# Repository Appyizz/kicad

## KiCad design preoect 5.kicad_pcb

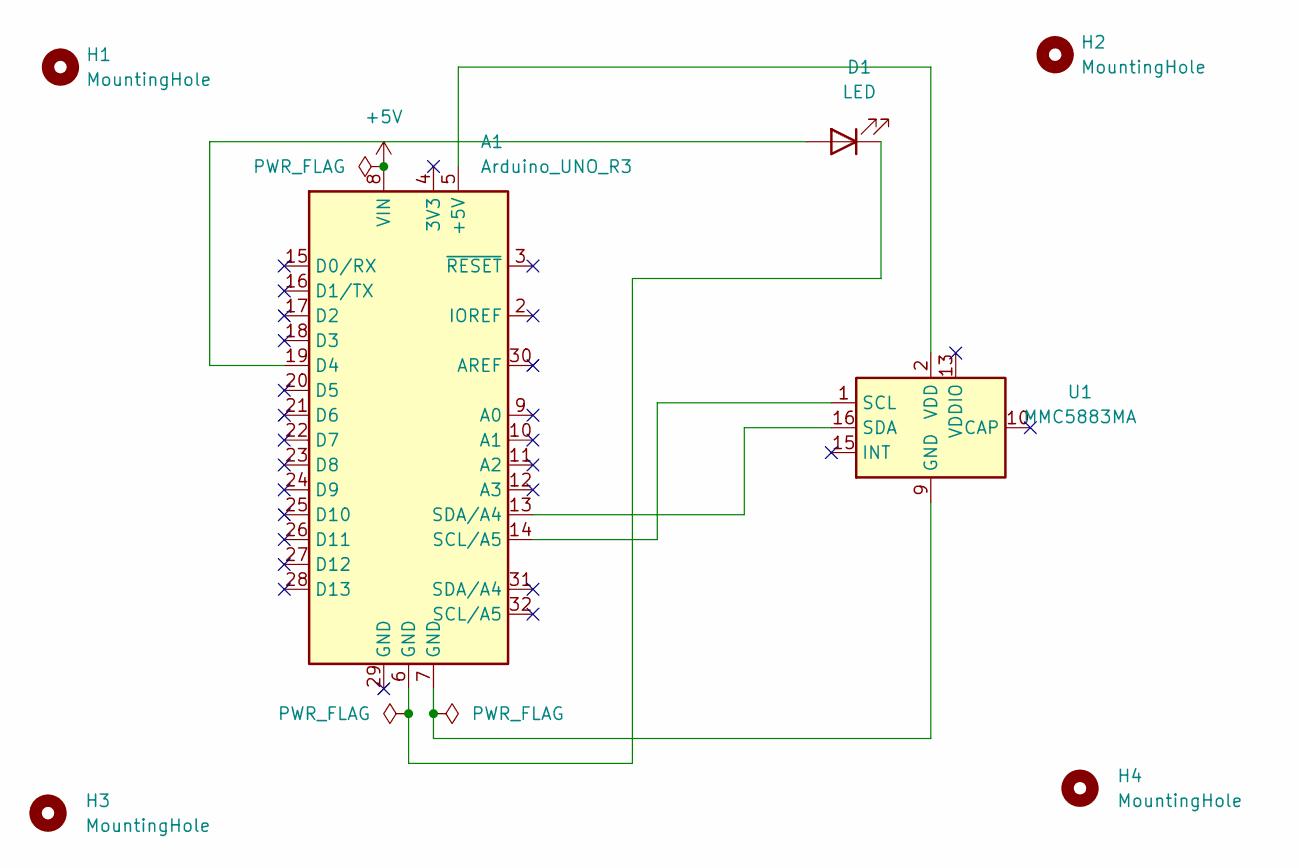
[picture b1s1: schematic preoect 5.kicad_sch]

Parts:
A1: Arduino_UNO_R3
D1: LED; LED_D4.0mm
H1, H2, H3, H4: MountingHole; MountingHole_2.5mm
U1: MMC5883MA; LGA-16_3x3mm_P0.5mm

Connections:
+5V: A1.8 (VIN)
unnamed: A1.5 (+5V), U1.2 (VDD)
unnamed: A1.19 (D4), D1.2 (A)
unnamed: A1.7 (GND), U1.9 (GND), U1.11 (GND)
unnamed: A1.6 (GND), D1.1 (K)
unnamed: A1.14 (SCL/A5), U1.1 (SCL)
unnamed: A1.13 (SDA/A4), U1.16 (SDA)

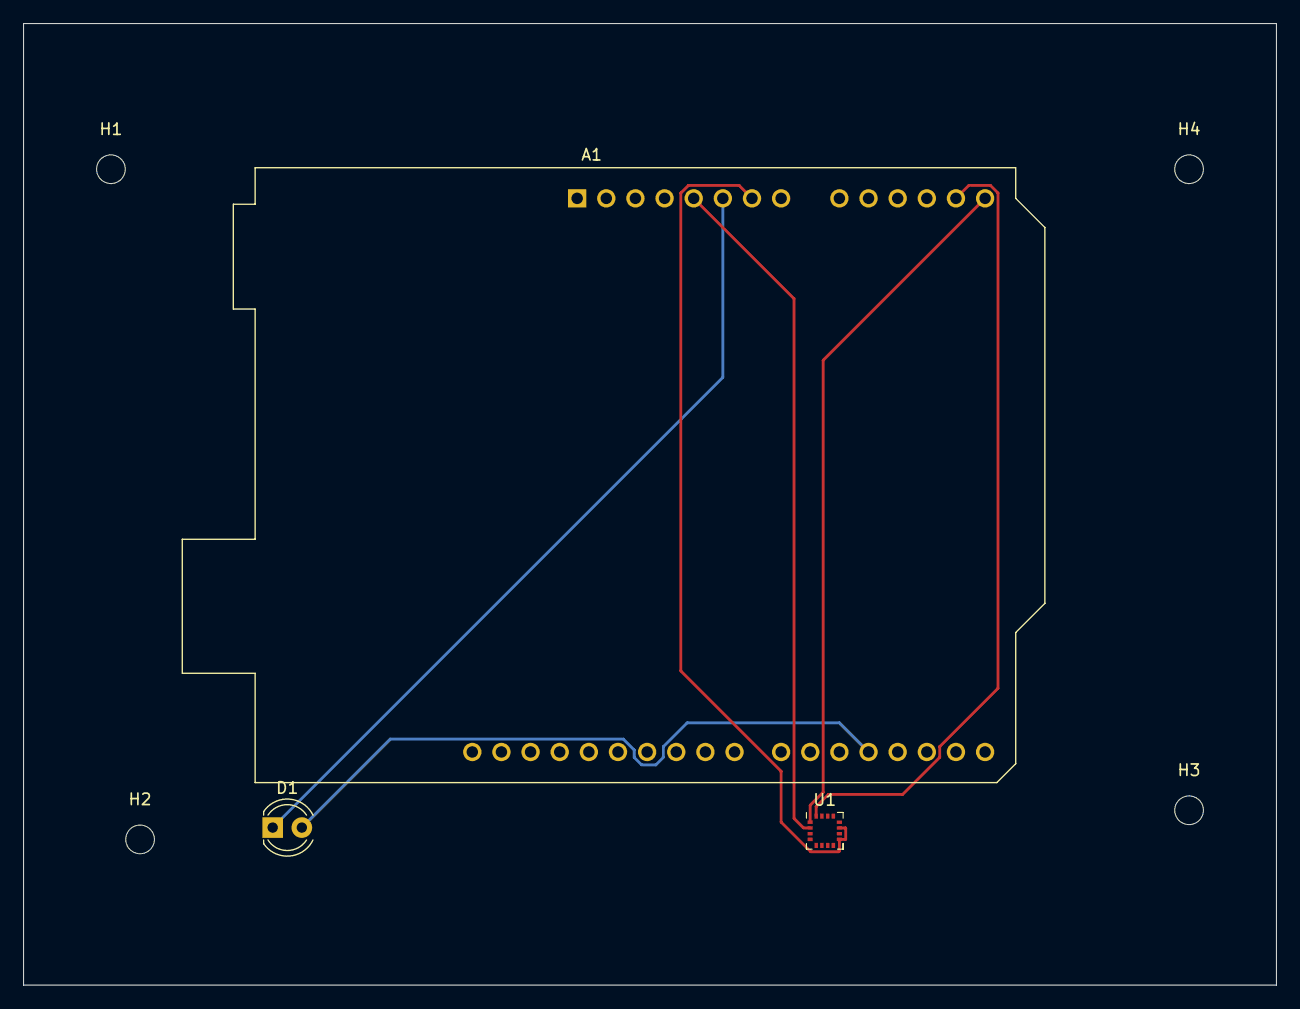
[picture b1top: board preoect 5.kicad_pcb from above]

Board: 2 copper layers, 109.2 x 83.8 mm, 7 parts (0 on the bottom side), 6 nets.

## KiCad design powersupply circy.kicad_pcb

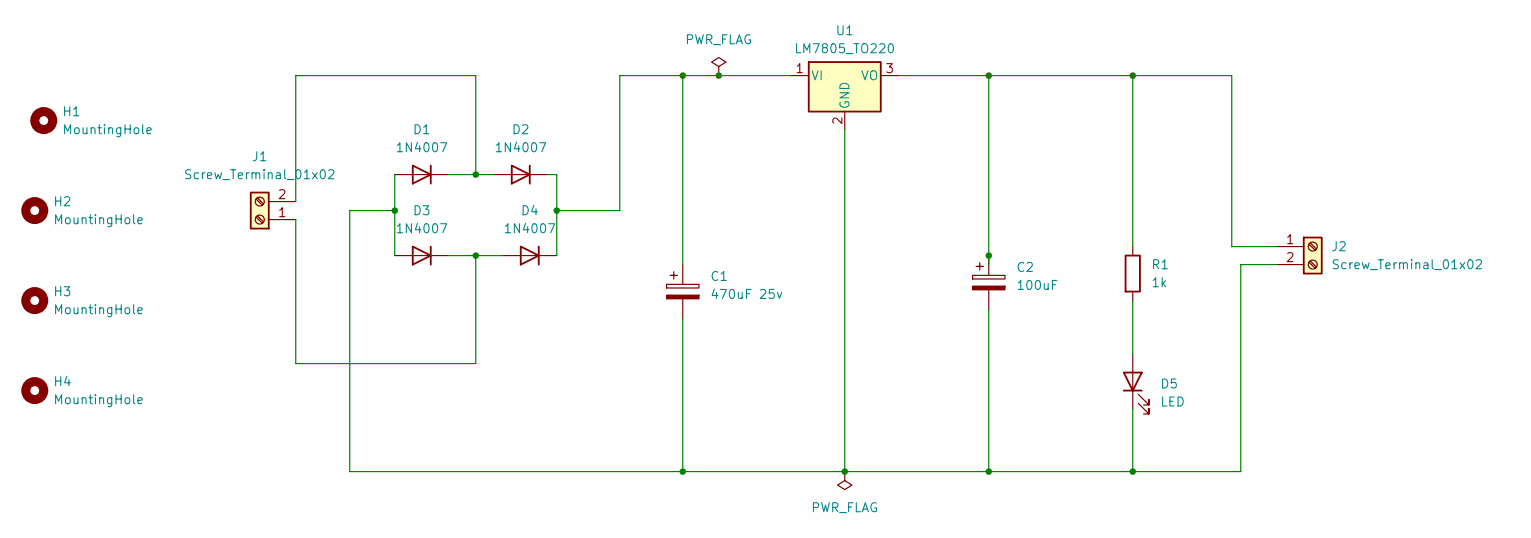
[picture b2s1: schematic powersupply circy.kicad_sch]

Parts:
C1: 470uF 25v; CP_Radial_D4.0mm_P1.50mm
C2: 100uF; CP_Radial_D4.0mm_P1.50mm
D1: 1N4007; D_DO-41_SOD81_P7.62mm_Horizontal
D2, D3, D4: 1N4007; D_DO-41_SOD81_P10.16mm_Horizontal
D5: LED; LED_D5.0mm
H1, H2, H3, H4: MountingHole; MountingHole_4.5mm
J1, J2: Screw_Terminal_01x02; TerminalBlock_Altech_AK300-4_P5.00mm
R1: 1k; R_Axial_Power_L20.0mm_W6.4mm_P22.40mm
U1: LM7805_TO220; TO-220-3_Vertical

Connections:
unnamed: C1.2, C2.2, D1.2 (A), D3.2 (A), D5.1 (K), J2.2, U1.2 (GND)
unnamed: D1.1 (K), D2.2 (A), J1.2
unnamed: C1.1, D2.1 (K), D4.1 (K), U1.1 (VI)
unnamed: D3.1 (K), D4.2 (A), J1.1
unnamed: D5.2 (A), R1.2
unnamed: C2.1, J2.1, R1.1, U1.3 (VO)

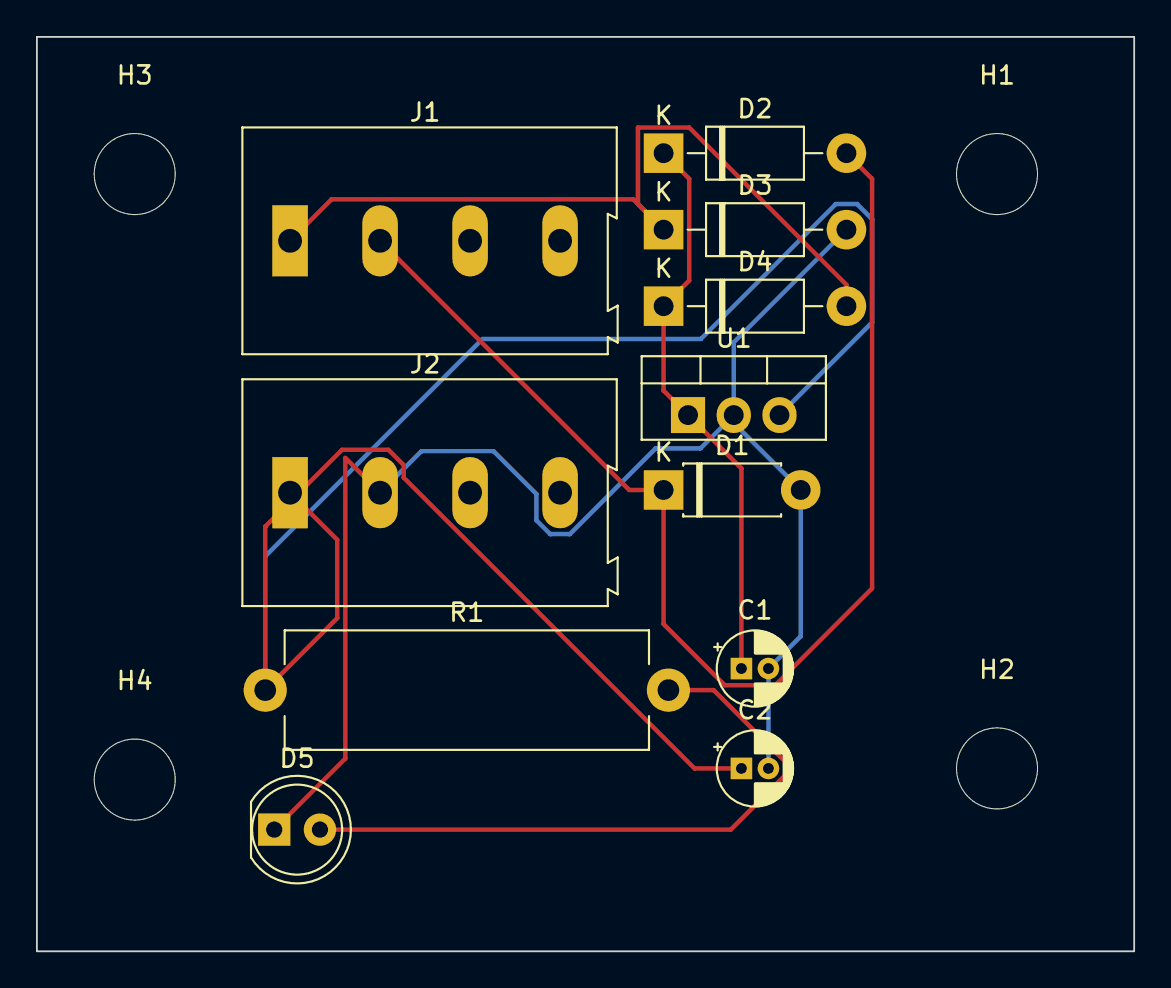
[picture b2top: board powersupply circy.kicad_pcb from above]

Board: 2 copper layers, 61.0 x 50.8 mm, 15 parts (0 on the bottom side), 6 nets.

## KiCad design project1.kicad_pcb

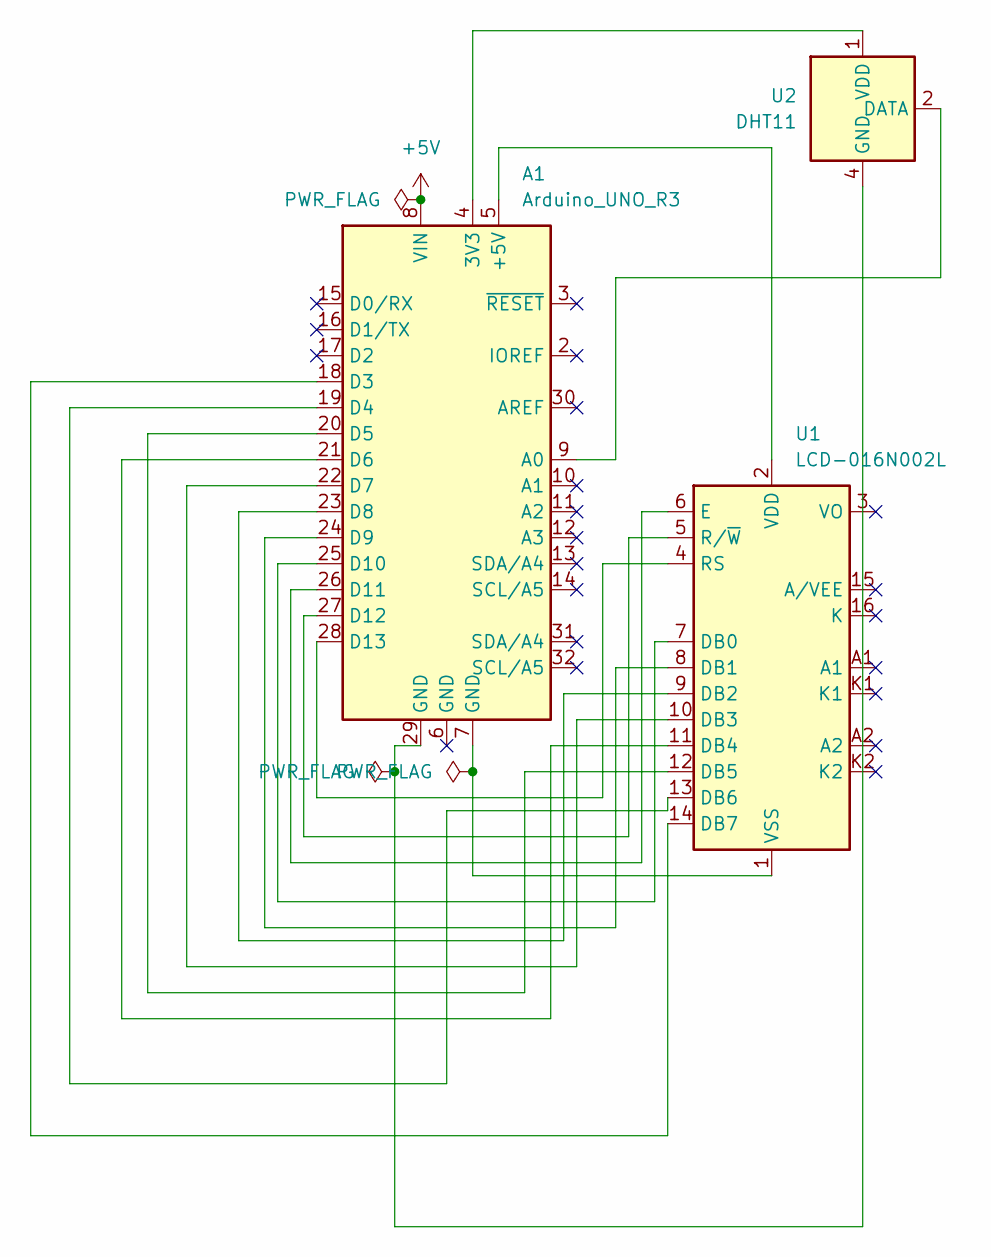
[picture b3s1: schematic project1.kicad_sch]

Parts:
A1: Arduino_UNO_R3
U1: LCD-016N002L
U2: DHT11; Aosong_DHT11_5.5x12.0_P2.54mm

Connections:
+5V: A1.8 (VIN)
unnamed: A1.4 (3V3), U2.1 (VDD)
unnamed: A1.5 (+5V), U1.2 (VDD)
unnamed: A1.9 (A0), U2.2 (DATA)
unnamed: A1.18 (D3), U1.14 (DB7)
unnamed: A1.19 (D4), U1.13 (DB6)
unnamed: A1.20 (D5), U1.12 (DB5)
unnamed: A1.21 (D6), U1.11 (DB4)
unnamed: A1.22 (D7), U1.10 (DB3)
unnamed: A1.23 (D8), U1.9 (DB2)
unnamed: A1.24 (D9), U1.8 (DB1)
unnamed: A1.25 (D10), U1.7 (DB0)
unnamed: A1.26 (D11), U1.6 (E)
unnamed: A1.27 (D12), U1.5 (R/~W)
unnamed: A1.28 (D13), U1.4 (RS)
unnamed: A1.7 (GND), U1.1 (VSS)
unnamed: A1.29 (GND), U2.4 (GND)

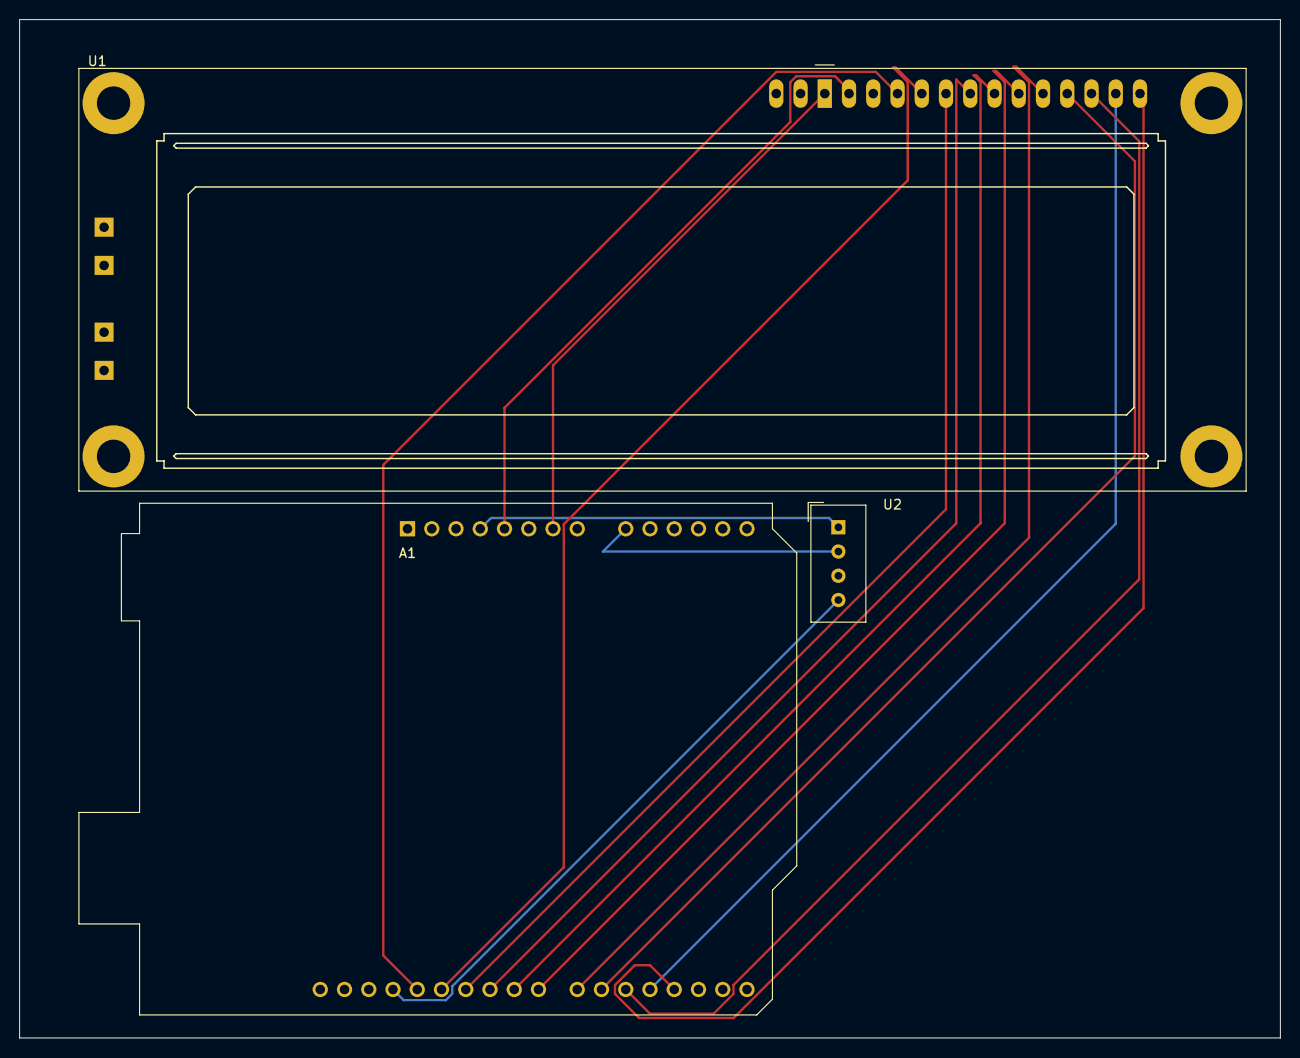
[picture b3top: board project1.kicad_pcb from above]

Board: 2 copper layers, 132.1 x 106.7 mm, 3 parts (0 on the bottom side), 16 nets.

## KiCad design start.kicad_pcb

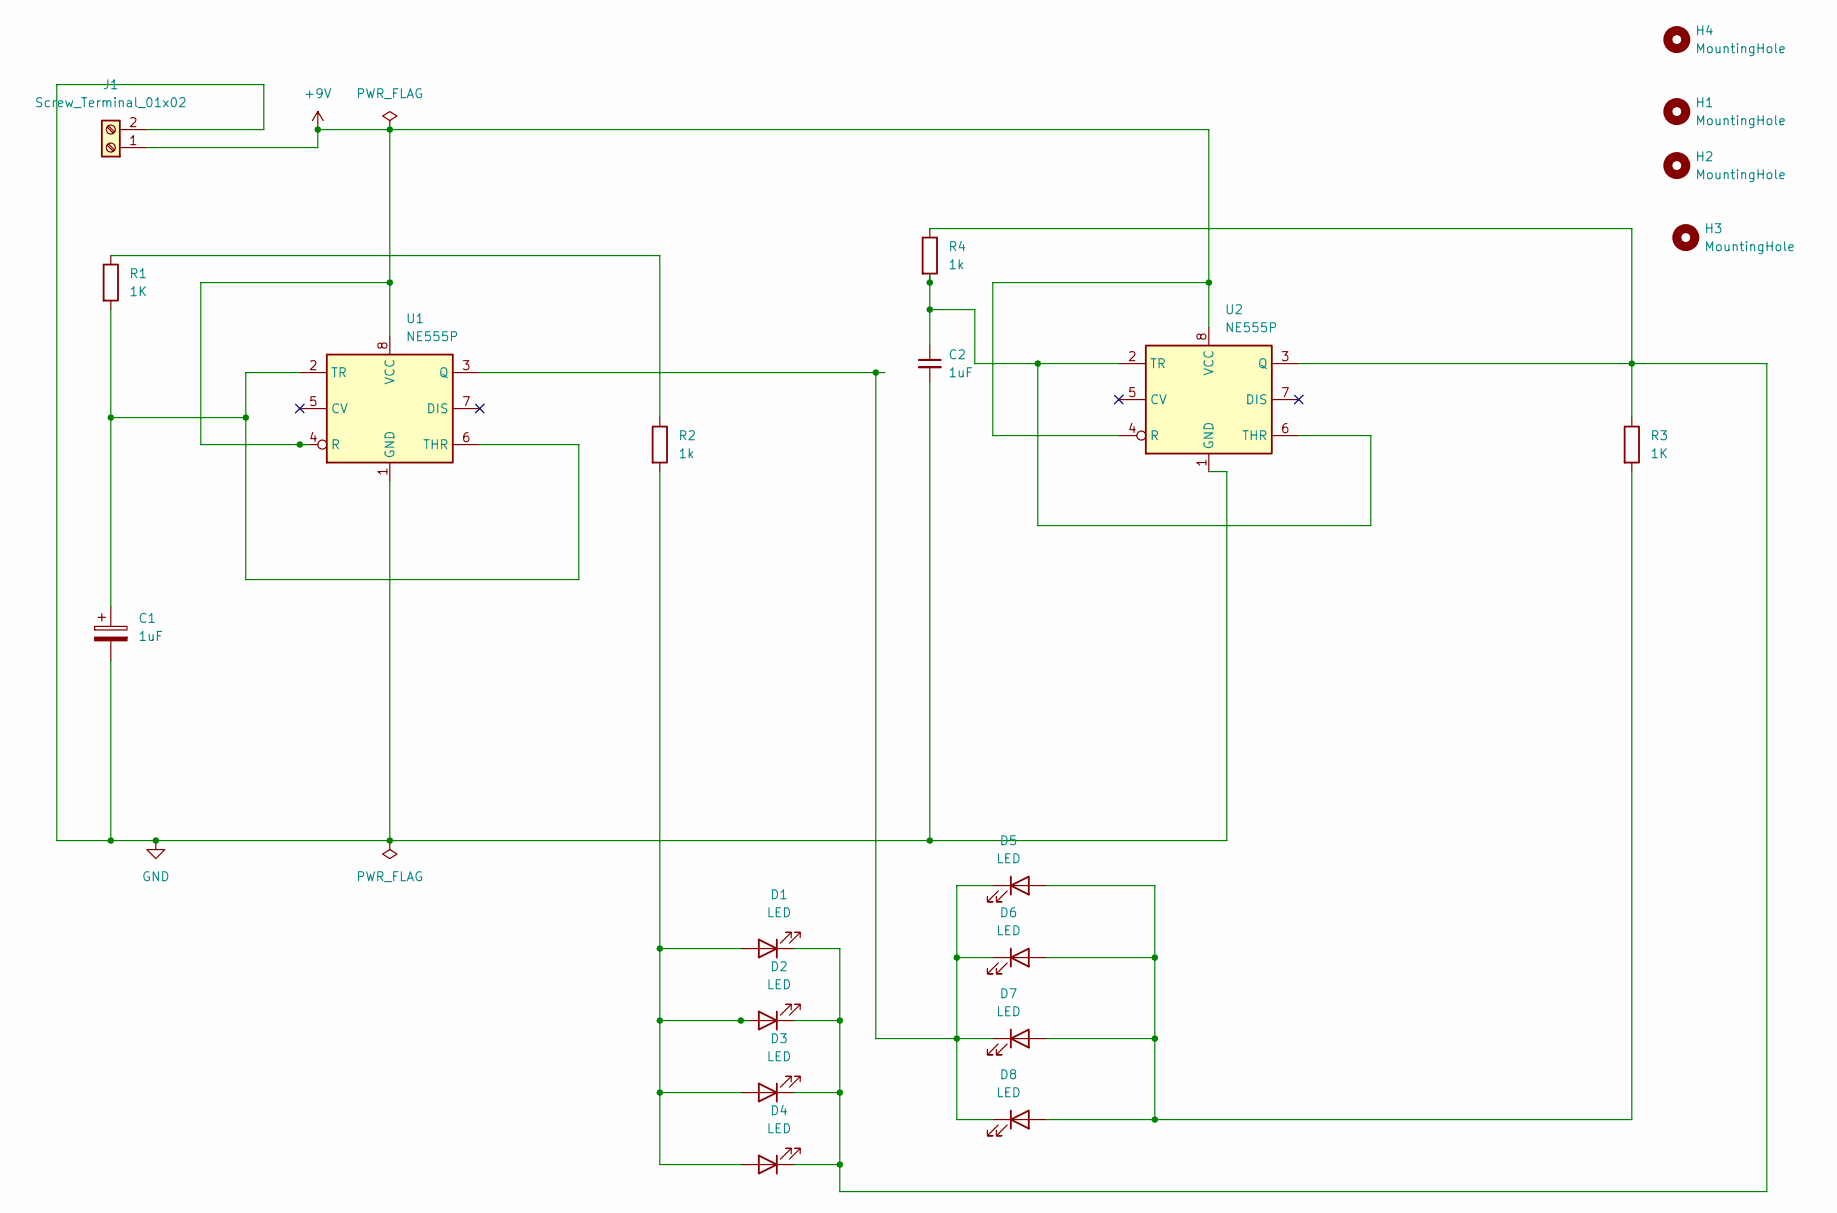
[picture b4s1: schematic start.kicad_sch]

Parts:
C1: 1uF; CP_Radial_D4.0mm_P1.50mm
C2: 1uF; C_Disc_D3.0mm_W1.6mm_P2.50mm
D1, D2, D3, D4, D5, D6, D7, D8: LED; LED_D3.0mm_Clear
H1, H2, H3, H4: MountingHole; MountingHole_2.1mm
J1: Screw_Terminal_01x02; TerminalBlock_bornier-2_P5.08mm
R1, R3: 1K; R_Axial_DIN0204_L3.6mm_D1.6mm_P5.08mm_Horizontal
R2, R4: 1k; R_Axial_DIN0204_L3.6mm_D1.6mm_P5.08mm_Horizontal
U1, U2: NE555P; DIP-8_W7.62mm

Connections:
+9V: J1.1, U1.4 (R), U1.8 (VCC), U2.4 (R), U2.8 (VCC)
GND: C1.2, C2.2, J1.2, U1.1 (GND), U2.1 (GND)
unnamed: D1.2 (A), D2.2 (A), D3.2 (A), D4.2 (A), R2.2
unnamed: D1.1 (K), D2.1 (K), D3.1 (K), D4.1 (K), R3.1, R4.1, U2.3 (Q)
unnamed: D5.2 (A), D6.2 (A), D7.2 (A), D8.2 (A), R3.2
unnamed: D5.1 (K), D6.1 (K), D7.1 (K), D8.1 (K), U1.3 (Q)
unnamed: R1.1, R2.1
unnamed: C1.1, R1.2, U1.2 (TR), U1.6 (THR)
unnamed: C2.1, R4.2, U2.2 (TR), U2.6 (THR)

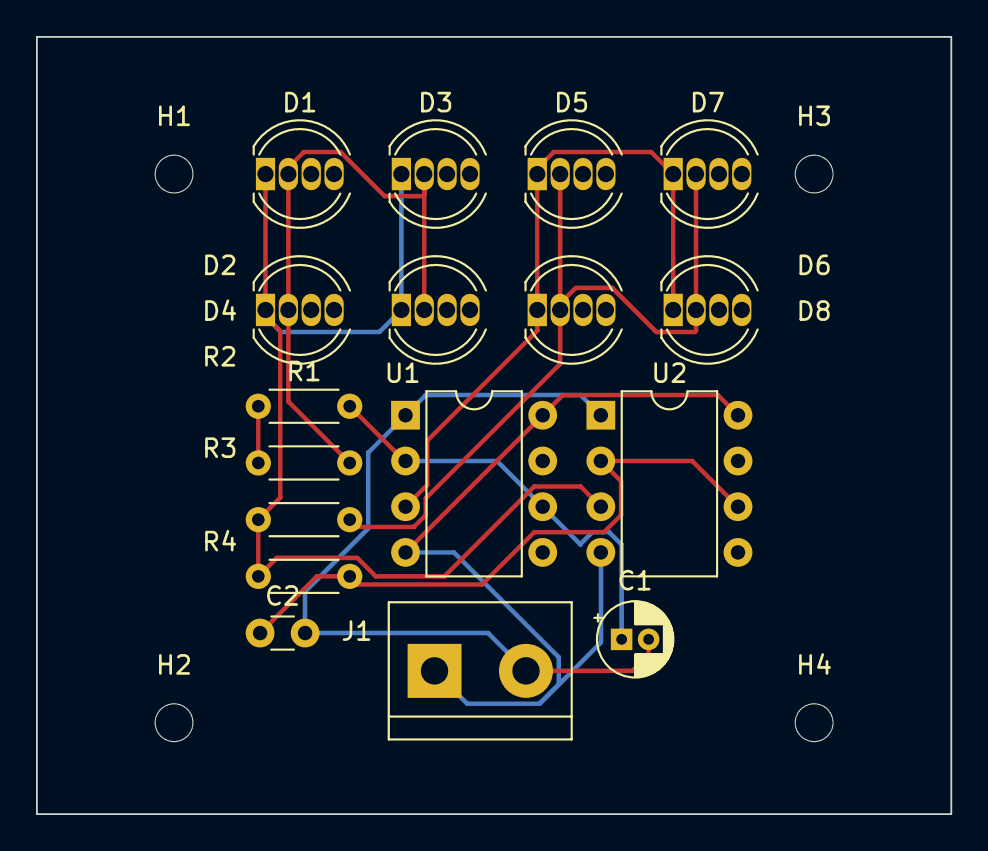
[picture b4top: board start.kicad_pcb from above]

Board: 2 copper layers, 50.8 x 43.2 mm, 21 parts (0 on the bottom side), 9 nets.

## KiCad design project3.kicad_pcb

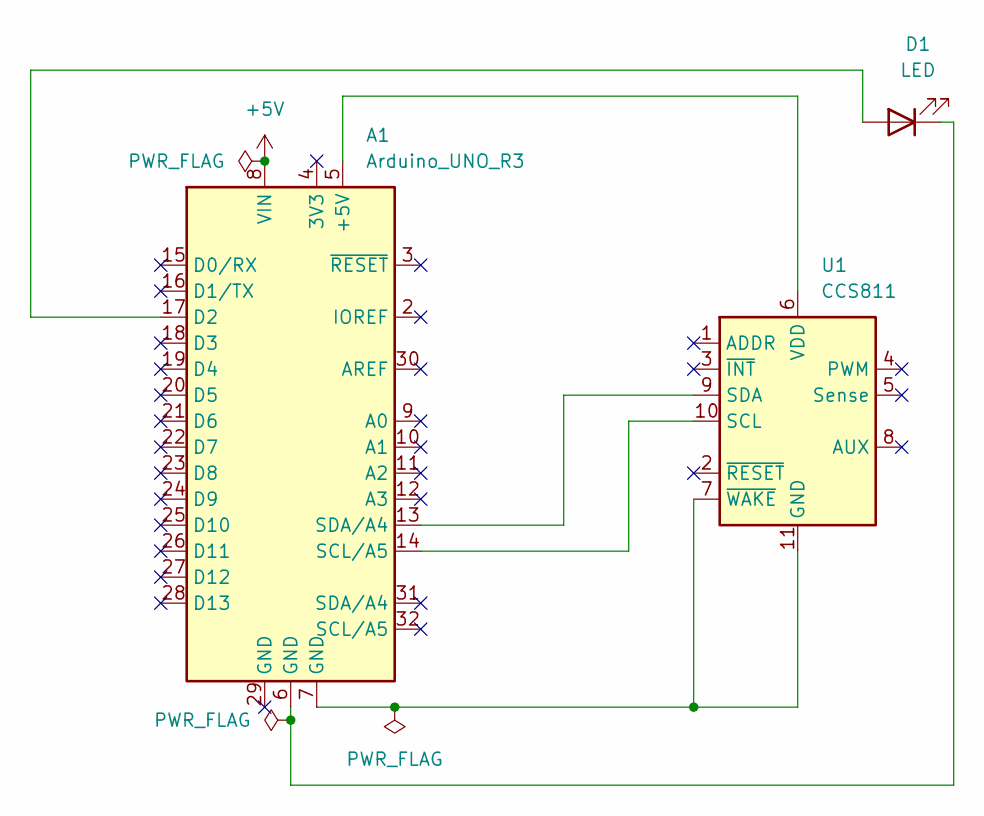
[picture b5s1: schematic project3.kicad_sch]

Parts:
A1: Arduino_UNO_R3
D1: LED; LED_D3.0mm
U1: CCS811; DIP-64_W25.4mm_Socket

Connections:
+5V: A1.8 (VIN)
unnamed: A1.5 (+5V), U1.6 (VDD)
unnamed: A1.17 (D2), D1.2 (A)
unnamed: A1.6 (GND), D1.1 (K)
unnamed: A1.7 (GND), U1.7 (~WAKE), U1.11 (GND)
unnamed: A1.14 (SCL/A5), U1.10 (SCL)
unnamed: A1.13 (SDA/A4), U1.9 (SDA)

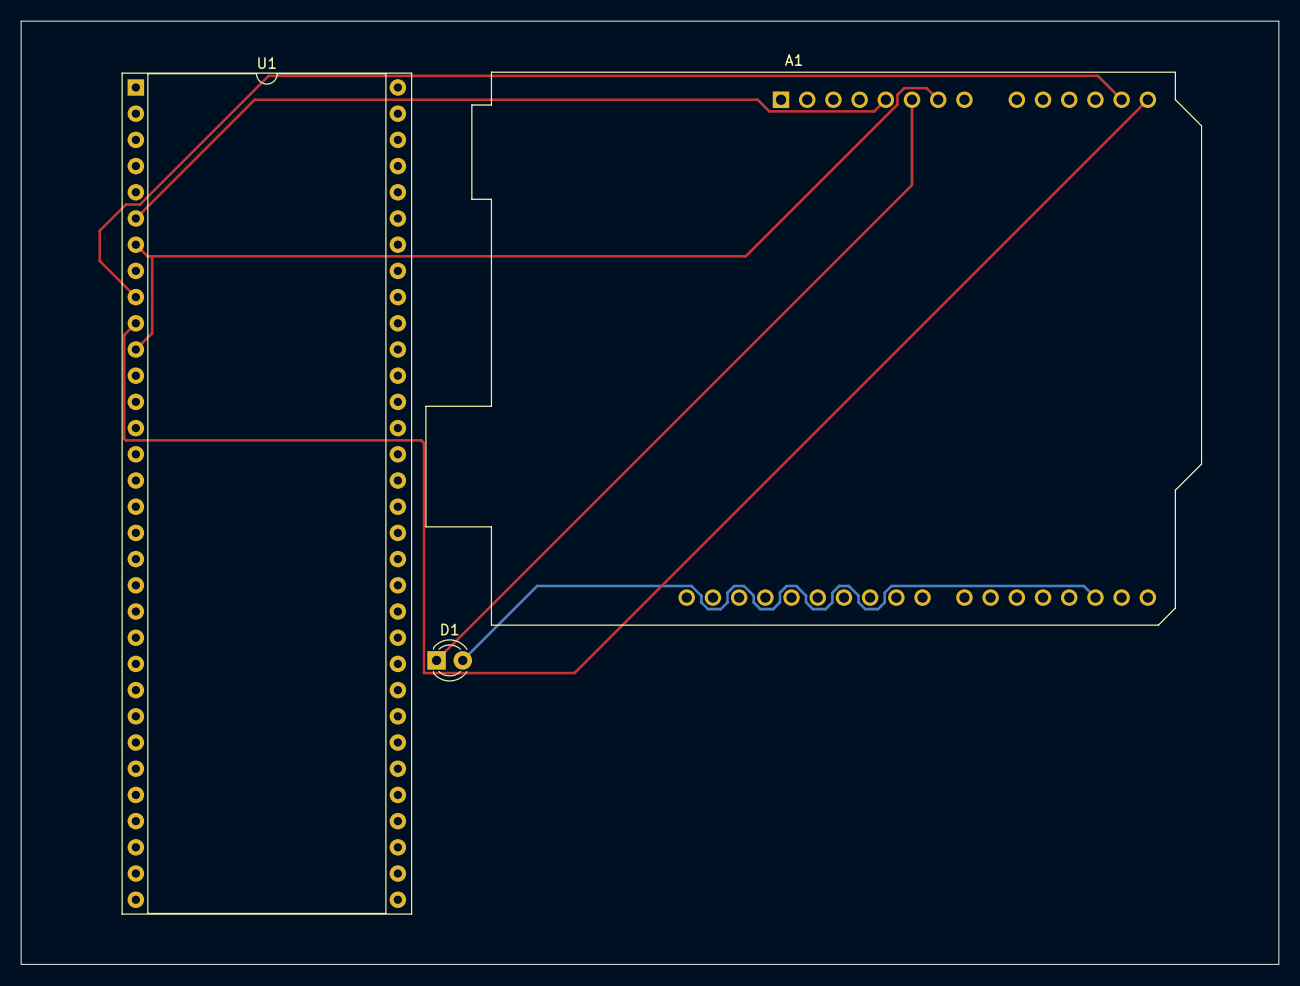
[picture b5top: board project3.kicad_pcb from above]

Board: 2 copper layers, 121.9 x 91.4 mm, 3 parts (0 on the bottom side), 6 nets.

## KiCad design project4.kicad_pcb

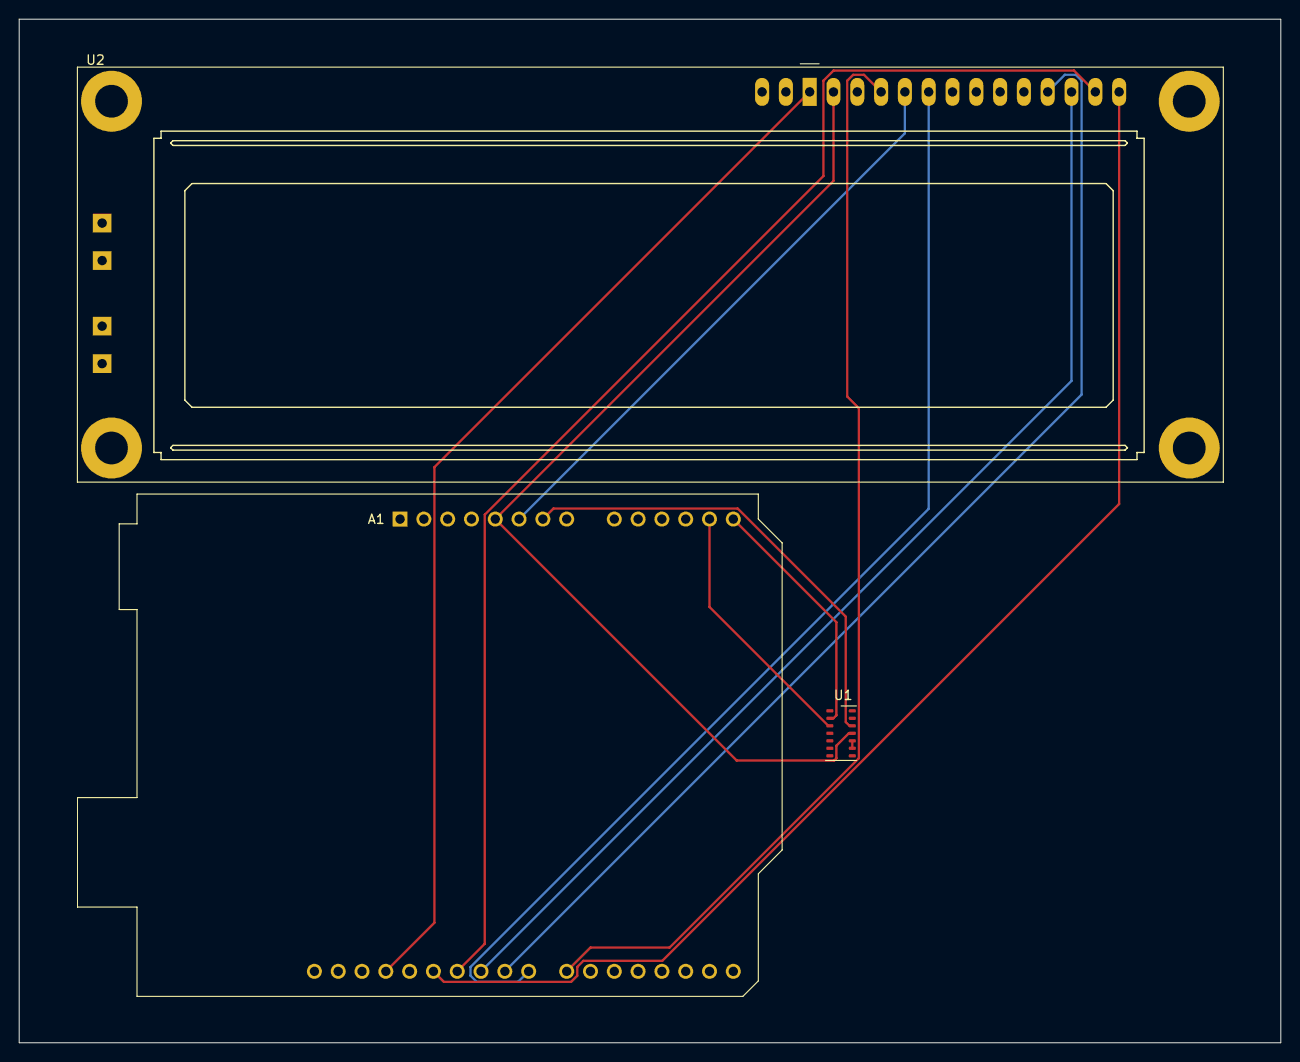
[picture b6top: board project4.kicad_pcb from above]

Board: 2 copper layers, 134.6 x 109.2 mm, 3 parts (0 on the bottom side), 12 nets.

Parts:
A1: Arduino_UNO_R3
U1: MAX30102; Maxim_OLGA-14_3.3x5.6mm_P0.8mm
U2: LCD-016N002L

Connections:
unnamed: A1.5 (+5V), U1.11 (VDD), U2.2 (VDD)
unnamed: A1.22 (D7), U2.4 (RS)
unnamed: A1.23 (D8), U2.6 (E)
unnamed: A1.24 (D9), U2.11 (DB4)
unnamed: A1.25 (D10), U2.12 (DB5)
unnamed: A1.26 (D11), U2.13 (DB6)
unnamed: A1.27 (D12), U2.14 (DB7)
unnamed: A1.7 (GND), U1.12 (GND)
unnamed: A1.14 (SCL/A5), U1.2 (SCL)
unnamed: A1.13 (SDA/A4), U1.3 (SDA)
unnamed: A1.6 (GND), U2.5 (R/~W)
unnamed: A1.29 (GND), U2.1 (VSS)

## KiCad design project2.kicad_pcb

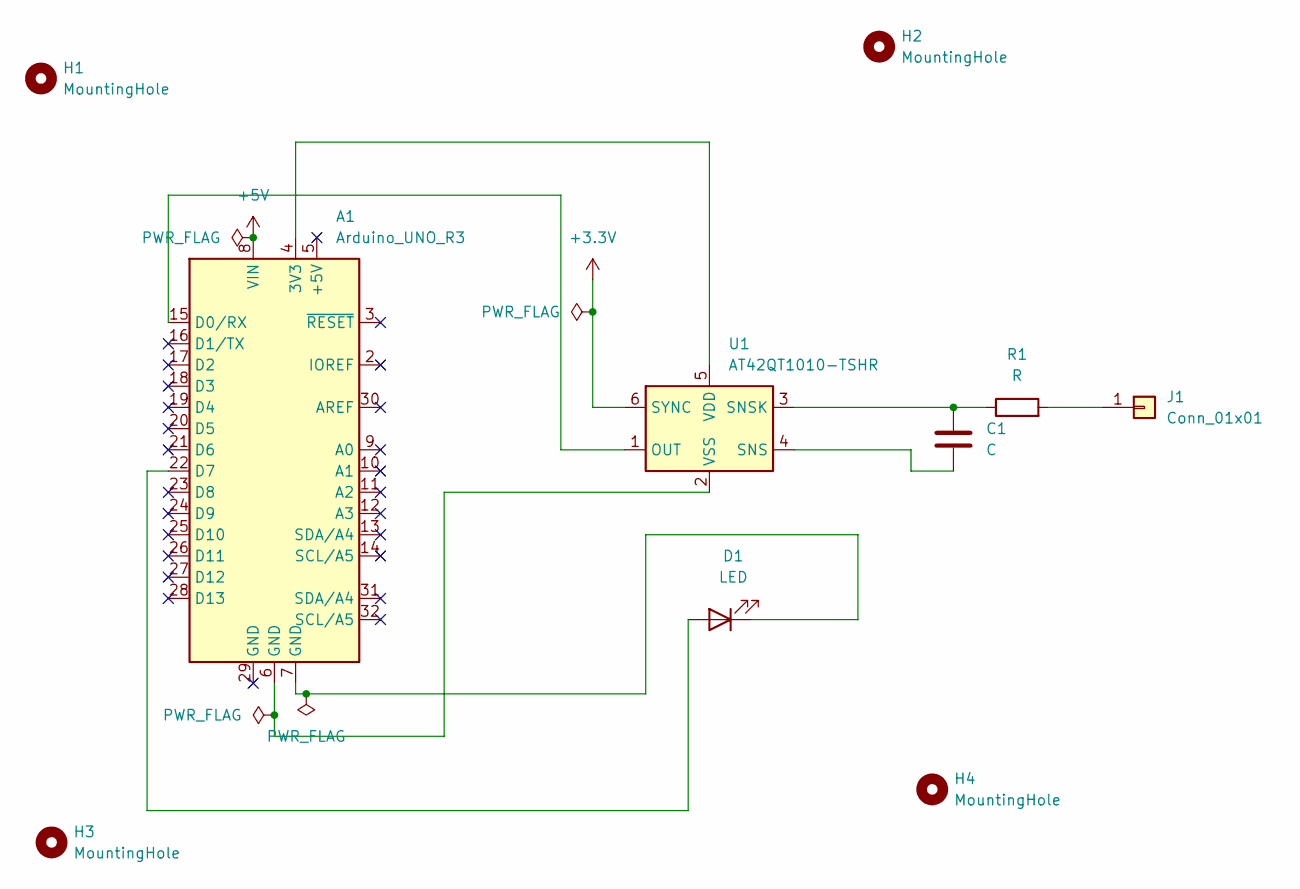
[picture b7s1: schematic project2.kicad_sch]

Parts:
A1: Arduino_UNO_R3
C1: C; CP_Radial_D4.0mm_P2.00mm
D1: LED; LED_D8.0mm
H1, H2, H3, H4: MountingHole; MountingHole_2.2mm_M2_ISO14580
J1: Conn_01x01; TerminalBlock_Phoenix_MKDS-1,5-2-5.08_1x02_P5.08mm_Horizont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
R1: R; R_Axial_DIN0516_L15.5mm_D5.0mm_P20.32mm_Horizontal
U1: AT42QT1010-TSHR; SOT-23-6

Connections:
+3.3V: U1.6 (SYNC)
+5V: A1.8 (VIN)
unnamed: A1.4 (3V3), U1.5 (VDD)
unnamed: A1.15 (D0/RX), U1.1 (OUT)
unnamed: A1.22 (D7), D1.2 (A)
unnamed: A1.7 (GND), D1.1 (K)
unnamed: J1.1, R1.2
unnamed: C1.2, U1.4 (SNS)
unnamed: C1.1, R1.1, U1.3 (SNSK)
unnamed: A1.6 (GND), U1.2 (VSS)

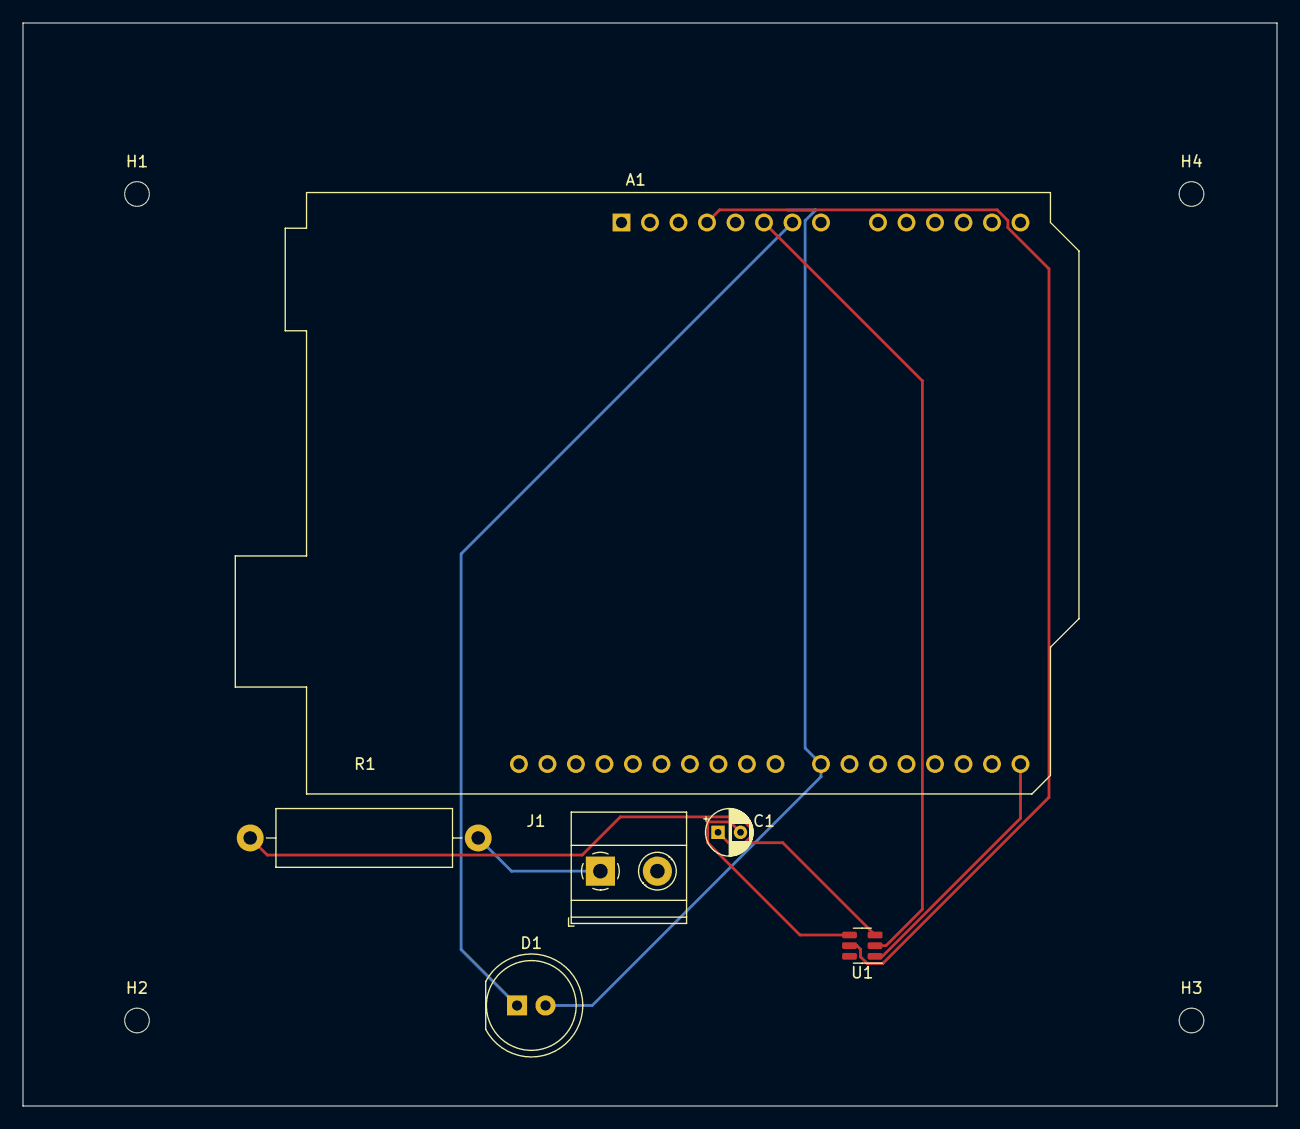
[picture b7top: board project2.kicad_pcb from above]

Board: 2 copper layers, 111.8 x 96.5 mm, 10 parts (0 on the bottom side), 8 nets.
